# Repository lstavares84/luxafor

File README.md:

# SIGNA

Luz de presença USB-C para a sala — e, se você quiser, para acompanhar suas IAs.

O **modo sala** lê o Google Agenda e o Outlook e mostra se você está livre, prestes a entrar em uma reunião ou ocupado. O aviso de “prestes a entrar” é configurável no app (padrão: 5 minutos). O **modo IA** é opt-in: monitora Claude, ChatGPT e Grok e indica ocioso, processando, precisa de atenção, erro, ou limite atingido (cota de 5 h ou semanal).

Em modo misto, os LEDs 3 e 2 (topo e meio) mostram a sala e o LED 1 (baixo) mostra a IA. **OCUPADO tem prioridade máxima** e trava os três LEDs em vermelho; no v1 o LED da IA some, e isso não é configurável.

O nome **SIGNA** é provisório, até a busca de marca no INPI.

> **Estado em 22/11/2026:** projeto de placa (rev D) verificado no KiCad 9.0.2 (ERC 0, DRC 0 erros). Montagem 3D integrada (placa + corpo + cabo) sem interferências não intencionais. Firmware compila (≈ 17,5 KB) e os testes de host passam. **Nada foi fabricado nem testado em silício.**

## Estados

Prioridade 1 é a mais alta.

| Prioridade | Modo | Estado | Cor | Comportamento |
|---|---|---|---|---|
| 1 | Sala | OCUPADO | `#FF3B2F` | contínuo 1,0; trava os 3 LEDs (`0xFF`) |
| 2 | Sala | PRESTES A ENTRAR | `#FF8A1A` | pulso lento de 3 s; padrão 5 min antes do evento |
| 3 | IA | ERRO | `#FF3FC8` | 2,5 Hz com pulso de 130 ms (abaixo do limite WCAG de 3 Hz) |
| 4 | IA | PRECISA DE ATENÇÃO | `#FFE02E` | onda quadrada 1 Hz |
| 5 | IA | PROCESSANDO | `#3D8BFF` | respiração 2,4 s |
| 6 | IA | LIMITE ATINGIDO | `#9B5CFF` | cota de 5 h: pulso duplo; cota semanal: contínuo 0,28 |
| 7 | Sala | LIVRE | `#2FD28A` | contínuo 0,28 |
| 8 | IA | IA DESOCUPADA | `#7C8EA6` | contínuo 0,08 |

A tabela completa, com curvas e alocação dos LEDs, está em [`software/data/produto.json`](software/data/produto.json) e no [caderno conceitual](docs/caderno-signa/signa-conceito.pdf).

## Mapa do repositório

| Caminho | O que é |
|---|---|
| [`hardware/revD/`](hardware/revD/) | Placa atual: KiCad 9, gerbers, BOM, renders, [`CHANGELOG.md`](hardware/revD/CHANGELOG.md) |
| [`mecanica/`](mecanica/) | Corpo plástico, berço, tampa, botão, cabo e o conjunto integrado |
| [`software/`](software/) | Firmware (STM32C071 + TinyUSB) e app de desktop (calendário, hooks, extensão) |
| [`docs/caderno-signa/`](docs/caderno-signa/) | Caderno conceitual SIGNA (14 lâminas A3) e os scripts que o geram |
| [`docs/caderno-engenharia/`](docs/caderno-engenharia/) | Caderno de engenharia SIGNA (141 lâminas A3), em [três partes](docs/caderno-engenharia/README.md), e o gerador |
| [`docs/prompts/`](docs/prompts/) | Prompts para cadernos: [conceitual](docs/prompts/prompt-caderno-conceitual.md), [conceitual genérico](docs/prompts/prompt-caderno-generico.md) e [engenharia](docs/prompts/prompt-caderno-engenharia.md) |
| [`docs/FUNCIONAMENTO.md`](docs/FUNCIONAMENTO.md) | Relatório da engenharia reversa do Luxafor Flag |
| [`PROTOCOLO.md`](PROTOCOLO.md) | Protocolo HID de 8 bytes (o SIGNA é compatível e o estende) |
| [`luxafor.py`](luxafor.py), [`tools/anim.py`](tools/anim.py) | CLI e ferramenta de medição do Flag original |
| [`.old/`](.old/) | Revisões e conceitos superados (rev A–C, caderno antigo, exploração de formas) |

## Placa rev D

11 × 44 mm (15,2 mm nas orelhas da ponta USB), FR-4 de 2 camadas e 0,8 mm. MCU STM32C071G8U6, 3× WS2816B-2020 (16 bits por canal, PWM 10 kHz), USB-C, botão S1 na borda de baixo e pontos de teste no verso.

O que entrou em relação à rev C, o delta de custo e as pendências: [`hardware/revD/CHANGELOG.md`](hardware/revD/CHANGELOG.md).

### Placa anotada

*Face de cima: LEDs WS2816B-2020, conversor de nível, MCU, LDO, USB-C e o botão S1 na borda de baixo.*

*Face de baixo: pads SWD (Tag-Connect), jumper BOOT0, pontos de teste (VBUS, dado dos LEDs, GND) e serigrafia «SIGNA rev D».*

## Montagem 3D

Conjunto integrado — PCB rev D, corpo plástico e cabo USB-C — em um único arquivo:

- [`mecanica/signa_conjunto.glb`](mecanica/signa_conjunto.glb) (~9 MB), para ver no navegador ([visualizador glTF](https://gltf-viewer.donmccurdy.com))
- [`mecanica/signa_conjunto.step`](mecanica/signa_conjunto.step) (~14 MB), para o CAD

Desenhos técnicos (A00, P01–P06), STEP/STL/3MF de cada peça e a BOM: [`mecanica/README.md`](mecanica/README.md).

<table>
  <tr>
    <td align="center" width="50%">
      <br>
      <strong>Em uso · OCUPADO</strong>
    </td>
    <td align="center" width="50%">
      <br>
      <strong>Em uso · LIVRE</strong>
    </td>
  </tr>
  <tr>
    <td align="center">
      <br>
      <strong>Isométrica</strong>
    </td>
    <td align="center">
      <br>
      <strong>Explodida</strong>
    </td>
  </tr>
  <tr>
    <td align="center">
      <br>
      <strong>Corte</strong>
    </td>
    <td align="center">
      <br>
      <strong>Encaixe USB-C</strong>
    </td>
  </tr>
</table>

## Software

Firmware e app estão em [`software/`](software/). Como compilar, gravar e configurar: [`software/docs/README.md`](software/docs/README.md). Arquitetura e protocolo: [`software/docs/arquitetura.md`](software/docs/arquitetura.md).

- **Firmware** (C, STM32C071G8U6 + TinyUSB): motor dos estados, WS2816 a 48 bits/LED, DFU na ROM, serial em flash. Compila em ≈ 17,5 KB de flash. A placa atual é a rev D (mesmos pinos de USB e LEDs da rev C; o S1 entra em PA14).
- **App** (Python 3.10+): daemon, CLI, bandeja, calendários Google e Outlook, hooks de Claude Code / Codex e extensão para ChatGPT, Claude e Grok na web.
- Compatível com o protocolo HID de 8 bytes do Luxafor Flag, com extensões (serial `0x51`/`0x52`/`0x62`, estados por LED).

Ainda não há teste em silício. O VID:PID padrão de desenvolvimento é `1209:0001` (pid.codes, só para prototipagem).

## Decisões em aberto

1. **Posição do botão.** Embaixo do pendente, é preciso segurar o tubo para apertar (a chave pede 1,6 N; o pendente pesa ~0,2 N). Alternativas: chave mais leve, ou o botão na tampa (exigiria flex ou fio).
2. **DFU pelo botão.** Só funciona se `nBOOT_SEL = 0` for gravado na produção. Isso se junta à decisão já aberta no software (`make AUTO_NBOOT_SEL=1` ou gravação dos option bytes).
3. **Cabo.** Para cotar: casca metálica do plugue exposta ≥ 5,8 mm, sobremoldagem ≤ 11,6 × 6,4 mm, capa Ø 3,5–4,0 mm. Vale pedir amostra ao fornecedor.
4. **Painel de fabricação.** A placa tem 15,2 mm de largura nas orelhas, e elas não podem quebrar na separação.
5. **Estoque do MCU.** A JLC tinha 109 unidades do STM32C071G8U6 em 22/11/2026: dá para os protótipos, fica apertado para produção. A alternativa GBU6 estava com estoque zero. Evitar as variantes com sufixo «N».
6. **VID:PID definitivo** e busca de marca **SIGNA** no INPI.
7. Ainda falta validar como os limites da web (5 h e semanal) das IAs são detectados.

## Engenharia reversa do Luxafor Flag

Este repositório começou como a engenharia reversa do [Luxafor Flag](https://luxafor.com/product/flag2/) (USB `04d8:f372`, firmware `0x3c`). Essa parte permanece e o SIGNA é compatível com o mesmo protocolo HID.

```bash
./luxafor.py version                 # firmware 0x3c
./luxafor.py color top blue          # LEDs: all | bottom | middle | top
./luxafor.py fade all green 20 --wait
./luxafor.py strobe all red 10 3
./luxafor.py wave 1 cyan 5 60
./luxafor.py pattern rainbow --wait
./luxafor.py off
```

Permissão: o usuário precisa de leitura e escrita em `/dev/hidrawN`.

**Cuidados com o Flag original:** `01 13 …` (endereço `0x13`) trava o firmware — reconecte o aparelho fisicamente; **não** use reset USB por software (`USBDEVFS_RESET`), que já travou o barramento do host. `0x51` e `0x52` **gravam o serial na NVM** (6 bytes e os 4 primeiros, respectivamente); `0x62` só lê. Não envie `0x51`/`0x52` em um aparelho cujo serial você queira preservar. Os opcodes `0x05` e `0x07`–`0x0F` não existem (não há resposta).

## Material antigo

Revisões de placa A–C, o caderno conceitual anterior e a exploração das quatro formas de produto estão em [`.old/`](.old/). Veja [`.old/README.md`](.old/README.md) para o que tem lá e por quê.

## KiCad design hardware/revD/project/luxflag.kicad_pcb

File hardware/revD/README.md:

# SIGNA, placa rev D (KiCad 9.0.2)

Evolução da rev C ([`.old/hardware/revC/`](../../.old/hardware/revC/)). **O que mudou e por quê: ver [`CHANGELOG.md`](CHANGELOG.md).** Tudo é gerado por script a partir de `tools/netlist.py`.
Apresentação completa, galeria e tabela de estados: ver o [README do repositório](../../README.md).

| Item | Valor |
|---|---|
| Placa | 11 × 44 mm (15,2 mm nas orelhas da ponta USB), FR-4, 2 camadas, 0,8 mm, 1 oz; USB-C sobressai 0,65 mm |
| Botão | S1 ALPS SKRTLAE010 lateral (C110293) na borda de baixo + R5 1 kΩ para PA14: OCUPADO/LIVRE manual e DFU ao ligar |
| Teste | TP1 VBUS, TP2 dado LEDs 5 V, TP3 GND (face de baixo) |
| LEDs | 3× **WS2816B-2020** (Worldsemi, LCSC C4154877): 16 bit/canal + gamma 4 bit, PWM 10 kHz, 20 mA (R+G+B), 6 pinos com dado duplo BI/BO |
| MCU | STM32C071G8U6 (UFQFPN-28 4×4, C44521811), USB FS sem cristal, DFU na ROM |
| Nível | SN74AHCT1G125DBVR (TI, SOT-23-5, C7484): VIH 2 V com VCC 5 V; WS2816 exige VIH ≥ 0,7×VDD = 3,5 V |
| Energia | VBUS 5 V nos LEDs e no buffer; AP2112K-3.3 (C51118) no MCU. Consumo estimado ≤ ~70 mA (3 × 20 mA + MCU) |
| USB | HRO TYPE-C-31-M-12 (C165948), CC1/CC2 5,1 kΩ, USBLC6-2SC6 (C7519) |
| SWD / BOOT0 | Tag-Connect TC2030-IDC-NL na face de baixo; JP1 (jumper de solda NA) + R4 1 kΩ puxam PA14/BOOT0 a 3V3 |
| Verificação | ERC 0. DRC 0 erros, 0 pendências, paridade OK; 1 aviso (silk do USB-C editado de propósito) |
| Roteamento | Freerouting 2.1.0 (DSN/SES, `-mt 1`, MP=80), 342 trilhas, 24 vias, + [`fix_vias.py`](tools/fix_vias.py) + remoção de trechos duplicados e pontas soltas |

## Ligação dos LEDs (datasheet WS2816B-2020, "Typical Application Circuit")
`U3.Y → R3 33 Ω → D1.DI`; `D1.BI = GND`; `Dn.DO → Dn+1.DI`; `Dn.BO → Dn+1.BI`; `D3.DO` e `D3.BO` livres.
Firmware: 48 bits por LED (G16 R16 B16, MSB primeiro), T0H 200–320 ns, T1H 520–800 ns, reset > 280 µs.

## Regenerar
```
cd tools
python3 gen_sch.py
python3 models3d.py             # modelos 3D próprios em ../lib/3d
MP=80 ./route.sh -mt 1         # placa (com orelhas) + DSN + Freerouting + SES + fix_vias + limpeza + GND + DRC
# (retrofit_outline.py só troca o Edge.Cuts de uma placa já roteada, sem rerotear)
python3 export_jlc.py          # fab/gerber.zip, bom.csv, cpl.csv
kicad-cli sch export pdf -o ../luxflag-schematic.pdf ../project/luxflag.kicad_sch
bash render_views.sh && python3 finish_views.py   # vistas 3D + close-ups
bash copper_views.sh                              # camadas de cobre (SVG -> PNG via Chrome)
python3 annotate.py                               # renders anotados
python3 parts_check.py                            # estoque LCSC/JLC -> docs/parts-check.json
```
O Freerouting 2.1.0 (jar) não vai no pacote: baixe de github.com/freerouting/freerouting/releases.

## Pendências
1. Rotação do CPL na prévia da JLC (U1–U4, J1, D1–D3).
2. Footprint do WS2816B-2020 feito pelo datasheet; conferir na prévia.
3. BOOT0 (JP1 ou botão S1 ao ligar) só vale com `nBOOT_SEL = 0`; com flash vazia entra em DFU sozinho.
5. Painel: considerar as orelhas (15,2 mm) no trilho/V-cut.
6. Firmware: botão lido pelo IDR de PA14 em modo SWCLK (ver CHANGELOG).
4. Pinos 18/19 = PA11[PA9]/PA12[PA10]: confirmar remapeamento no firmware.
5. Modelos 3D de U1, J1 e LEDs nos renders são substitutos visuais.
6. Par USB sem impedância controlada (FS, < 15 mm).

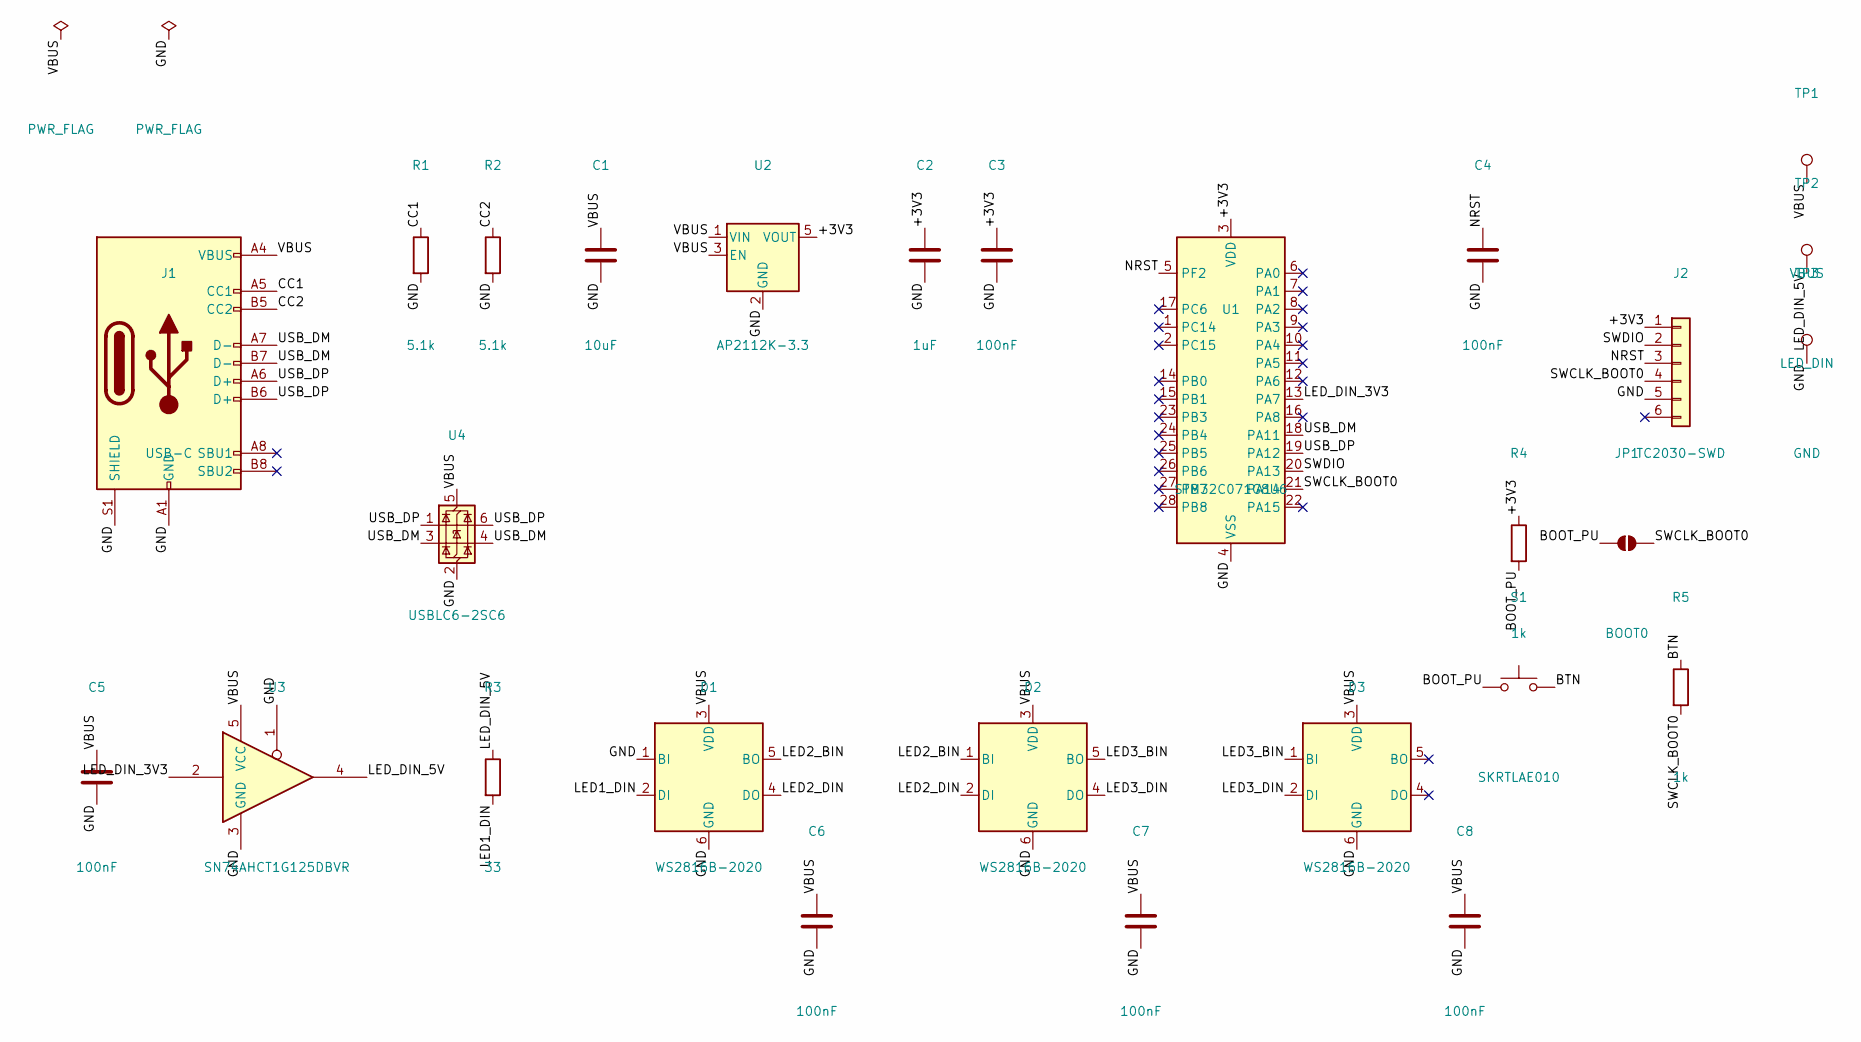
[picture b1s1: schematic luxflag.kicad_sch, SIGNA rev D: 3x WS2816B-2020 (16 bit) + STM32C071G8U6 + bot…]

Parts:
C1: 10uF; C_0603_1608Metric; LCSC C19702
C2: 1uF; C_0402_1005Metric; LCSC C52923
C3, C4, C5, C6, C7, C8: 100nF; C_0402_1005Metric; LCSC C1525
D1, D2, D3: WS2816B-2020; LED_WS2816B-2020_2.2x2.0mm; LCSC C4154877
J1: USB-C; USB_C_Receptacle_HRO_TYPE-C-31-M-12; LCSC C165948
J2: TC2030-SWD; Tag-Connect_TC2030-IDC-NL_2x03_P1.27mm_Vertical
JP1: BOOT0; SolderJumper-2_P1.3mm_Open_RoundedPad1.0x1.5mm
R1, R2: 5.1k; R_0402_1005Metric; LCSC C25905
R3: 33; R_0402_1005Metric; LCSC C25105
R4, R5: 1k; R_0402_1005Metric; LCSC C11702
S1: SKRTLAE010; SW_SKRTLAE010_JLC; LCSC C110293
TP1: VBUS; TestPoint_Pad_D1.0mm
TP2: LED_DIN; TestPoint_Pad_D1.0mm
TP3: GND; TestPoint_Pad_D1.0mm
U1: STM32C071G8U6; QFN-28_4x4mm_P0.5mm; LCSC C44521811
U2: AP2112K-3.3; SOT-23-5; LCSC C51118
U3: SN74AHCT1G125DBVR; SOT-23-5; LCSC C7484
U4: USBLC6-2SC6; SOT-23-6; LCSC C7519

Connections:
/+3V3: C2.1, C3.1, J2.1, R4.1, U1.3 (VDD), U2.5 (VOUT)
/BOOT_PU: JP1.1 (A), R4.2, S1.1
/BTN: R5.1, S1.2
/CC1: J1.A5 (CC1), R1.1
/CC2: J1.B5 (CC2), R2.1
/GND: C1.2, C2.2, C3.2, C4.2, C5.2, C6.2, C7.2, C8.2, D1.1 (BI), D1.6 (GND), D2.6 (GND), D3.6 (GND), J1.A1 (GND), J1.A12 (GND), J1.B1 (GND), J1.B12 (GND), J1.S1 (SHIELD), J2.5, R1.2, R2.2, TP3.1, U1.4 (VSS), U2.2 (GND), U3.1, U3.3 (GND), U4.2 (GND)
/LED1_DIN: D1.2 (DI), R3.2
/LED2_BIN: D1.5 (BO), D2.1 (BI)
/LED2_DIN: D1.4 (DO), D2.2 (DI)
/LED3_BIN: D2.5 (BO), D3.1 (BI)
/LED3_DIN: D2.4 (DO), D3.2 (DI)
/LED_DIN_3V3: U1.13 (PA7), U3.2
/LED_DIN_5V: R3.1, TP2.1, U3.4
/NRST: C4.1, J2.3, U1.5 (PF2)
/SWCLK_BOOT0: J2.4, JP1.2 (B), R5.2, U1.21 (PA14)
/SWDIO: J2.2, U1.20 (PA13)
/USB_DM: J1.A7 (D-), J1.B7 (D-), U1.18 (PA11), U4.3 (I/O2), U4.4 (I/O2)
/USB_DP: J1.A6 (D+), J1.B6 (D+), U1.19 (PA12), U4.1 (I/O1), U4.6 (I/O1)
/VBUS: C1.1, C5.1, C6.1, C7.1, C8.1, D1.3 (VDD), D2.3 (VDD), D3.3 (VDD), J1.A4 (VBUS), J1.A9 (VBUS), J1.B4 (VBUS), J1.B9 (VBUS), TP1.1, U2.1 (VIN), U2.3 (EN), U3.5 (VCC), U4.5 (VBUS)

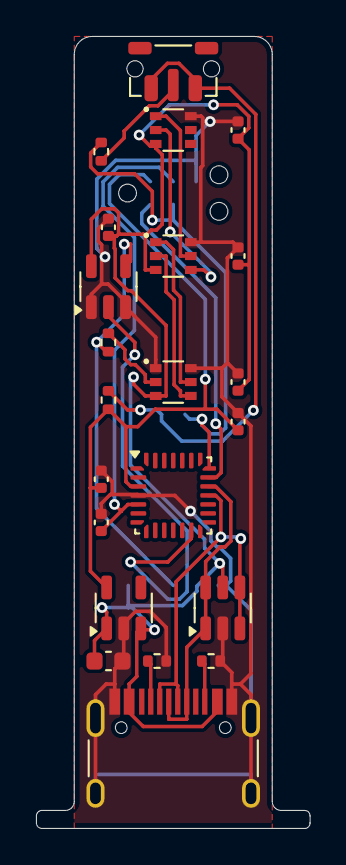
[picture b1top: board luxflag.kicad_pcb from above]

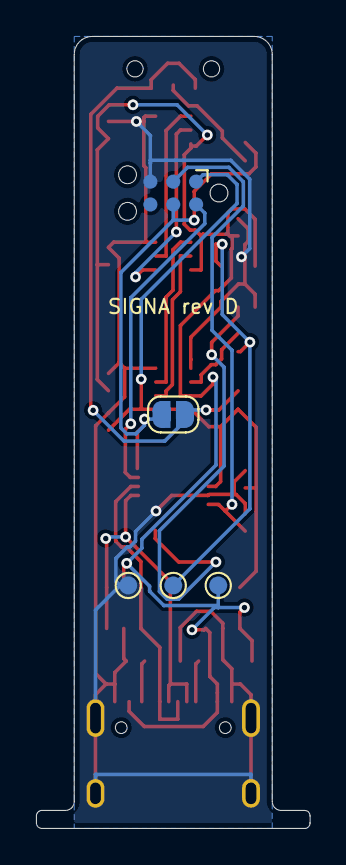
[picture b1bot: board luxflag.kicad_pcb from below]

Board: 2 copper layers, 15.2 x 44.0 mm, 27 parts (5 on the bottom side), 19 nets.

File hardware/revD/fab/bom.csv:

Comment,Designator,Footprint,LCSC
10uF,C1,C_0603_1608Metric,C19702
1uF,C2,C_0402_1005Metric,C52923
100nF,"C3,C4,C5,C6,C7,C8",C_0402_1005Metric,C1525
WS2816B-2020,"D1,D2,D3",LED_WS2816B-2020_2.2x2.0mm,C4154877
USB-C,J1,USB_C_Receptacle_HRO_TYPE-C-31-M-12,C165948
5.1k,"R1,R2",R_0402_1005Metric,C25905
33,R3,R_0402_1005Metric,C25105
1k,"R4,R5",R_0402_1005Metric,C11702
SKRTLAE010,S1,SW_SKRTLAE010_JLC,C110293
STM32C071G8U6,U1,QFN-28_4x4mm_P0.5mm,C44521811
AP2112K-3.3,U2,SOT-23-5,C51118
SN74AHCT1G125DBVR,U3,SOT-23-5,C7484
USBLC6-2SC6,U4,SOT-23-6,C7519

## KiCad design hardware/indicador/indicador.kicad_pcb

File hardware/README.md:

# Hardware SIGNA

A placa atual é a **[rev D](revD/)**: STM32C071G8U6, 3× WS2816B-2020 (16 bits por canal), botão S1 na borda de baixo, pontos de teste no verso e orelhas na ponta do USB para travar a placa no berço.

| Item | Valor |
|---|---|
| Placa | 11 × 44 mm (15,2 mm nas orelhas), FR-4, 2 camadas, 0,8 mm |
| MCU | STM32C071G8U6 (UFQFPN-28), USB FS sem cristal, DFU na ROM |
| LEDs | 3× WS2816B-2020, dado em PA7 via SN74AHCT1G125 |
| Botão | S1 ALPS SKRTLAE010 em PA14: alterna OCUPADO/LIVRE; segurado ao ligar, entra em DFU (`nBOOT_SEL = 0`) |
| Estado | KiCad 9.0.2, ERC 0, DRC 0 erros — **ainda não fabricada nem testada em silício** |

Arquivos de fabricação, esquemático, BOM, gerbers, renders e o que mudou em relação à rev C: [`revD/README.md`](revD/README.md) e [`revD/CHANGELOG.md`](revD/CHANGELOG.md).

A montagem 3D integrada (placa + corpo + cabo) está em [`mecanica/`](../mecanica/).

Revisões anteriores (rev A / indicador, rev B e rev C) e as ferramentas da rev A foram para [`.old/hardware/`](../.old/hardware/).

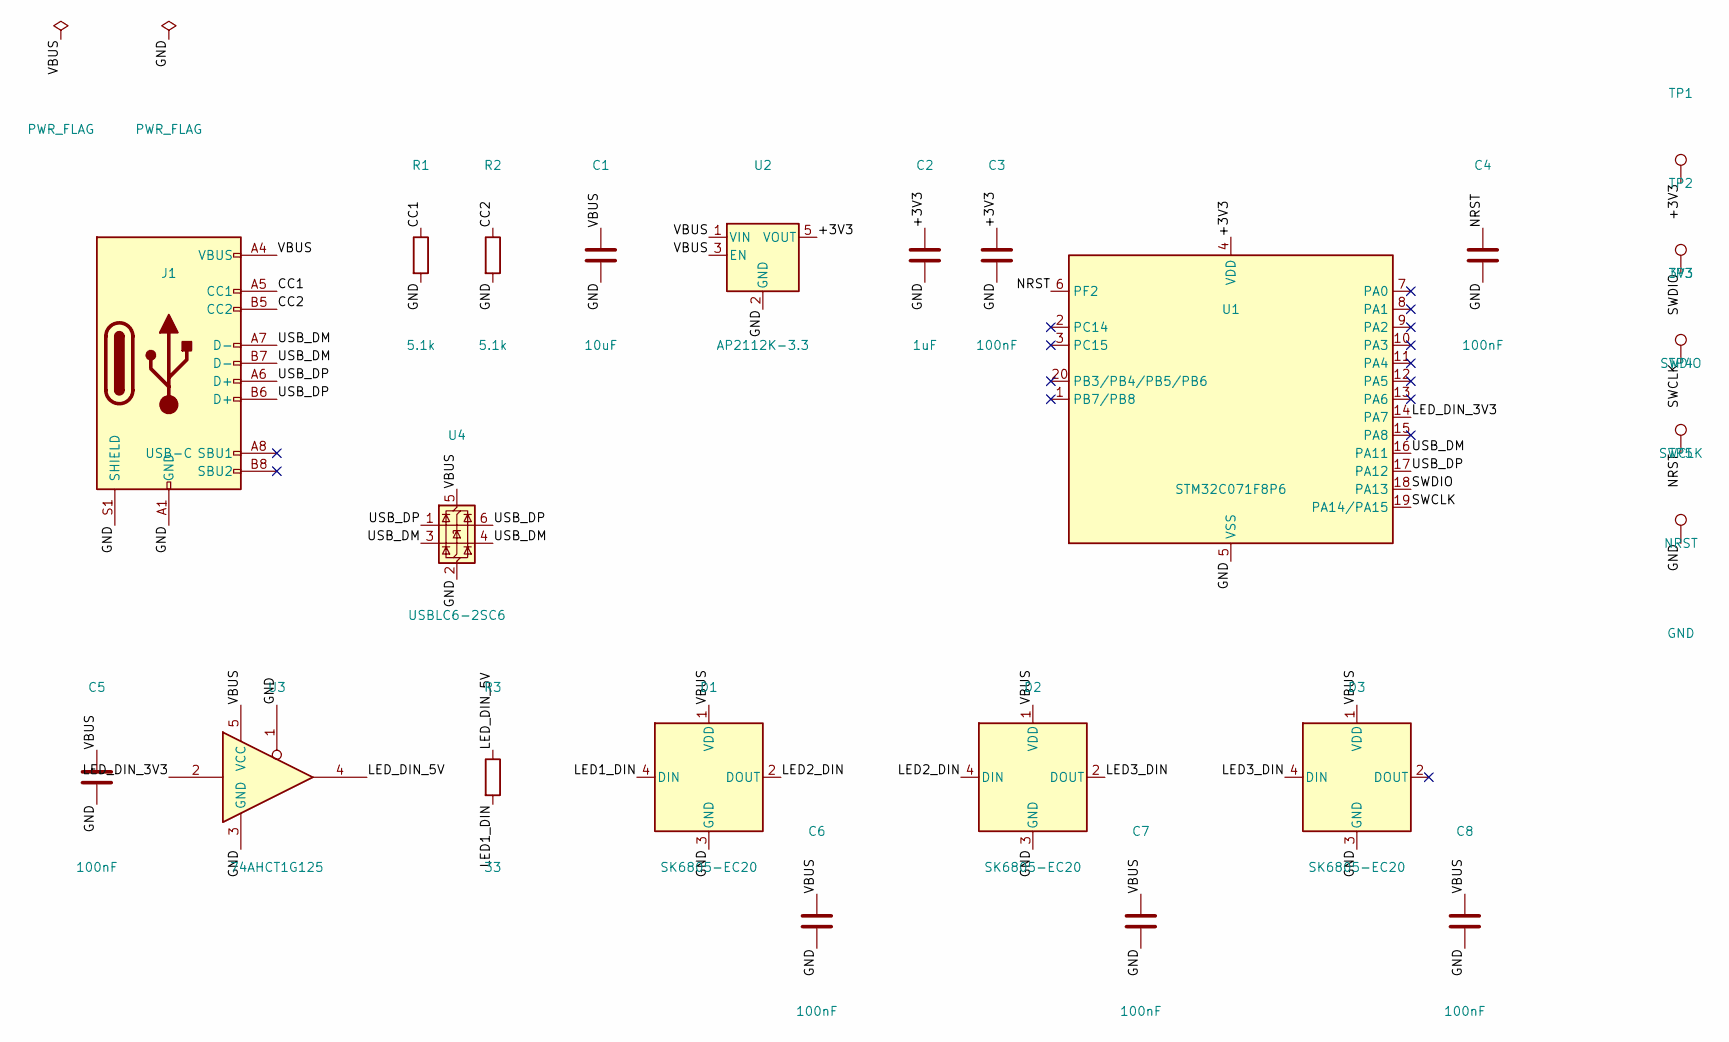
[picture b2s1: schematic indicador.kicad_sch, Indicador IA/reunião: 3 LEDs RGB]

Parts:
C1: 10uF; C_0603_1608Metric; LCSC C19702
C2: 1uF; C_0402_1005Metric; LCSC C52923
C3, C4, C5, C6, C7, C8: 100nF; C_0402_1005Metric; LCSC C1525
D1, D2, D3: SK6805-EC20; LED_SK6805-EC20_2.0x2.0mm; LCSC C2890036
J1: USB-C; USB_C_Receptacle_HRO_TYPE-C-31-M-12; LCSC C165948
R1, R2: 5.1k; R_0402_1005Metric; LCSC C25905
R3: 33; R_0402_1005Metric; LCSC C25105
TP1: 3V3; TestPoint_Pad_D1.0mm
TP2: SWDIO; TestPoint_Pad_D1.0mm
TP3: SWCLK; TestPoint_Pad_D1.0mm
TP4: NRST; TestPoint_Pad_D1.0mm
TP5: GND; TestPoint_Pad_D1.0mm
U1: STM32C071F8P6; TSSOP-20_4.4x6.5mm_P0.65mm; LCSC C43650205
U2: AP2112K-3.3; SOT-23-5; LCSC C51118
U3: 74AHCT1G125; SOT-353_SC-70-5; LCSC C53114384
U4: USBLC6-2SC6; SOT-23-6; LCSC C7519

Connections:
/+3V3: C2.1, C3.1, TP1.1, U1.4 (VDD), U2.5 (VOUT)
/CC1: J1.A5 (CC1), R1.1
/CC2: J1.B5 (CC2), R2.1
/GND: C1.2, C2.2, C3.2, C4.2, C5.2, C6.2, C7.2, C8.2, D1.3 (GND), D2.3 (GND), D3.3 (GND), J1.A1 (GND), J1.A12 (GND), J1.B1 (GND), J1.B12 (GND), J1.S1 (SHIELD), R1.2, R2.2, TP5.1, U1.5 (VSS), U2.2 (GND), U3.1, U3.3 (GND), U4.2 (GND)
/LED1_DIN: D1.4 (DIN), R3.2
/LED2_DIN: D1.2 (DOUT), D2.4 (DIN)
/LED3_DIN: D2.2 (DOUT), D3.4 (DIN)
/LED_DIN_3V3: U1.14 (PA7), U3.2
/LED_DIN_5V: R3.1, U3.4
/NRST: C4.1, TP4.1, U1.6 (PF2)
/SWCLK: TP3.1, U1.19 (PA14/PA15)
/SWDIO: TP2.1, U1.18 (PA13)
/USB_DM: J1.A7 (D-), J1.B7 (D-), U1.16 (PA11), U4.3 (I/O2), U4.4 (I/O2)
/USB_DP: J1.A6 (D+), J1.B6 (D+), U1.17 (PA12), U4.1 (I/O1), U4.6 (I/O1)
/VBUS: C1.1, C5.1, C6.1, C7.1, C8.1, D1.1 (VDD), D2.1 (VDD), D3.1 (VDD), J1.A4 (VBUS), J1.A9 (VBUS), J1.B4 (VBUS), J1.B9 (VBUS), U2.1 (VIN), U2.3 (EN), U3.5 (VCC), U4.5 (VBUS)

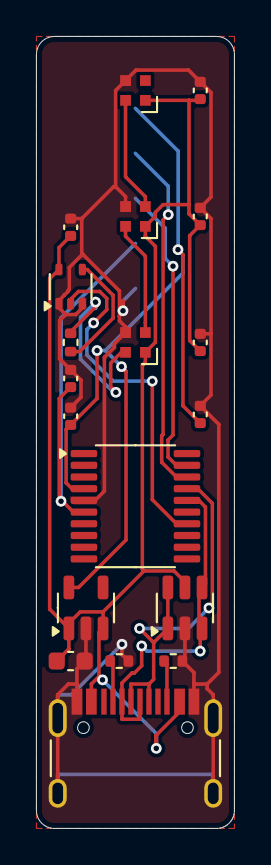
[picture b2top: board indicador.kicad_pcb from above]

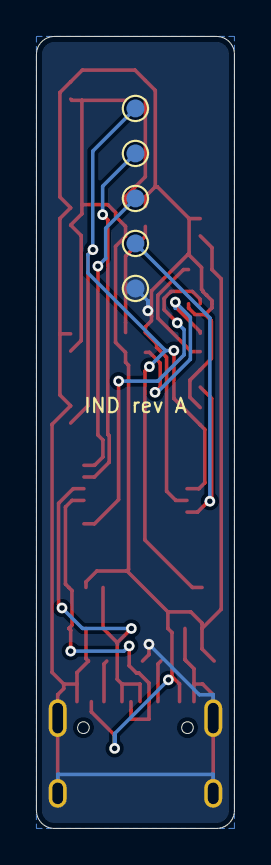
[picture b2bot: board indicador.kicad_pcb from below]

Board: 2 copper layers, 11.0 x 44.0 mm, 24 parts (5 on the bottom side), 15 nets.

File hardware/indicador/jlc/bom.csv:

Comment,Designator,Footprint,LCSC
10uF,C1,C_0603_1608Metric,C19702
1uF,C2,C_0402_1005Metric,C52923
100nF,"C3,C4,C5,C6,C7,C8",C_0402_1005Metric,C1525
SK6805-EC20,"D1,D2,D3",LED_SK6805-EC20_2.0x2.0mm,C2890036
USB-C,J1,USB_C_Receptacle_HRO_TYPE-C-31-M-12,C165948
5.1k,"R1,R2",R_0402_1005Metric,C25905
33,R3,R_0402_1005Metric,C25105
STM32C071F8P6,U1,TSSOP-20_4.4x6.5mm_P0.65mm,C43650205
AP2112K-3.3,U2,SOT-23-5,C51118
74AHCT1G125,U3,SOT-353_SC-70-5,C53114384
USBLC6-2SC6,U4,SOT-23-6,C7519

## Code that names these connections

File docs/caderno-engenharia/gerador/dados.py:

"""Leitura das fontes de engenharia. Nada inventado: se faltar, o chamador marca 'a definir'."""
import csv, json, os, sys

ROOT = os.path.dirname(os.path.abspath(__file__))


def _pasta(env, relativos, reserva):
    """Caminho da fonte: SIGNA_* se definida; senão a pasta deste repositório; senão /workspace."""
    v = os.environ.get(env, '').strip()
    if v:
        return v
    raiz = os.path.abspath(os.path.join(ROOT, '..', '..', '..'))
    for rel in relativos:
        p = os.path.join(raiz, rel)
        if os.path.isdir(p):
            return p
    return reserva


REV_D = _pasta('SIGNA_REVD', ('hardware/revD',), '/workspace/luxpcb-revD')
SW = _pasta('SIGNA_SW', ('software',), '/workspace/signa-sw')
MECH = _pasta('SIGNA_MECH', ('mecanica',), '/workspace/signa-3d')
CONC = _pasta('SIGNA_CONC', ('docs/caderno-signa', '.old/docs/conceito'), '/workspace/caderno-revC')

produto = json.load(open(os.path.join(CONC, 'dados/produto.json')))
jlc_revd = json.load(open(os.path.join(REV_D, 'docs/jlc_revD_2026-11-22.json')))
estoque = json.load(open(os.path.join(REV_D, 'docs/estoque_stm32c071.json')))
parts = json.load(open(os.path.join(REV_D, 'docs/parts-check.json')))
folgas_doc = json.load(open(os.path.join(MECH, 'docs/verificacao_montagem.json')))

# BOM eletrônica (fab)
bom_elec = list(csv.DictReader(open(os.path.join(REV_D, 'fab/bom.csv'))))
cpl = list(csv.DictReader(open(os.path.join(REV_D, 'fab/cpl.csv'))))

# BOM completa do produto
bom_prod = list(csv.DictReader(open(os.path.join(MECH, 'bom/bom_completa.csv'))))

modos = {m['id']: m for m in produto['modos']}
MODOS_PRIO = [modos[i] for i in produto['prioridade_ordem']]

# Pinagem UFQFPN-28 GP (DS14693, figura do encapsulamento _GxU, não N)
MCU_PINS = [
    (1, 'PC14-OSCX_IN', 'NC', 'não conectar'),
    (2, 'PC15-OSCX_OUT', 'NC', 'não conectar'),
    (3, 'VDD/VDDA', '+3V3', 'alimentação do MCU (U2)'),
    (4, 'VSS/VSSA', 'GND', 'terra'),
    (5, 'PF2-NRST', 'NRST', 'reset; C4 100 nF a GND; J2 pino 3'),
    (6, 'PA0', 'NC', 'não conectar'),
    (7, 'PA1', 'NC', 'não conectar'),
    (8, 'PA2', 'NC', 'não conectar'),
    (9, 'PA3', 'NC', 'não conectar'),
    (10, 'PA4', 'NC', 'não conectar'),
    (11, 'PA5', 'NC', 'não conectar'),
    (12, 'PA6', 'NC', 'não conectar'),
    (13, 'PA7', 'LED_DIN_3V3', 'SPI1_MOSI (AF0) → U3.A; dado dos LEDs'),
    (14, 'PB0', 'NC', 'não conectar'),
    (15, 'PB1', 'NC', 'não conectar'),
    (16, 'PA8', 'NC', 'não conectar'),
    (17, 'PC6', 'NC', 'no GP é PC6; na versão N este pino é VDDIO2 — não trocar'),
    (18, 'PA11 [PA9]', 'USB_DM', 'USB FS D− (padrão no UFQFPN-28; não remapear)'),
    (19, 'PA12 [PA10]', 'USB_DP', 'USB FS D+ (padrão; não remapear)'),
    (20, 'PA13', 'SWDIO', 'J2 pino 2'),
    (21, 'PA14-BOOT0', 'SWCLK_BOOT0', 'SWCLK + BOOT0; S1/R5 e JP1; J2 pino 4'),
    (22, 'PA15', 'NC', 'não conectar'),
    (23, 'PB3', 'NC', 'não conectar'),
    (24, 'PB4', 'NC', 'não conectar'),
    (25, 'PB5', 'NC', 'não conectar'),
    (26, 'PB6', 'NC', 'não conectar'),
    (27, 'PB7', 'NC', 'não conectar'),
    (28, 'PB8', 'NC', 'não conectar'),
]

# Preços JLC da BOM completa (já por produto)
def money(v):
    try:
        return float(v)
    except Exception:
        return None

# estados nativos firmware
ESTADOS_FW = [
    (0, 'apagado', '—', '—', 'LEDs apagados'),
    (1, 'LIVRE', '#2FD28A', 'fixo 0,28', 'SALA'),
    (2, 'PRESTES A ENTRAR', '#FF8A1A', 'respiração 3,0 s, piso 0,20, expoente 1,4', 'SALA'),
    (3, 'OCUPADO', '#FF3B2F', 'fixo 1,0', 'SALA'),
    (4, 'IA DESOCUPADA', '#7C8EA6', 'fixo 0,08', 'IA'),
    (5, 'PROCESSANDO', '#3D8BFF', 'respiração 2,4 s, piso 0,15, expoente 1,6', 'IA'),
    (6, 'PRECISA DE ATENÇÃO', '#FFE02E', 'quadrada 1 Hz, 50 %, piso 0,06', 'IA'),
    (7, 'ERRO', '#FF3FC8', 'estrobo 2,5 Hz, pulso 130 ms, piso 0,04', 'IA'),
    (8, 'LIMITE 5 h', '#9B5CFF', 'pulso duplo a cada 3 s (250/250/250 ms) a 0,55, piso 0,06', 'IA'),
    (9, 'LIMITE semanal', '#9B5CFF', 'fixo 0,28', 'IA'),
]

# Itens em aberto / a definir (só o que as fontes não fecham)
A_DEFINIR = [
    ('Nome comercial', 'SIGNA é provisório até verificação no INPI.'),
    ('VID:PID USB', 'Padrão de desenvolvimento 1209:0001 (Test PID do pid.codes). Par definitivo a decidir (pid.codes próprio, VID USB-IF ou sublicença). Nunca usar 04d8:f372 em unidade vendida.'),
    ('String USB do produto', 'O firmware ainda identifica o produto como "SIGNA rev C" (usb_ids.h).'),
    ('Byte de versão 0x80', 'Manter 0x3C (compatível com software antigo) ou usar um valor próprio. A versão real do SIGNA sai no 0x1F (hoje 0.1).'),
    ('nBOOT_SEL na produção', 'Precisa ser gravado como 0 para o DFU pelo botão/JP1 funcionar depois da 1.ª gravação. Processo de fábrica a definir (CubeProgrammer ou make AUTO_NBOOT_SEL=1).'),
    ('Posição do botão', 'S1 + P06 ficam embaixo do pendente. A chave pede 1,6 N e o produto pesa cerca de 0,2 N: é preciso segurar o tubo para apertar. Alternativas (chave mais leve ou botão na tampa, que exigiria flex ou fio) estão em aberto.'),
    ('Gesto longo do botão', 'O CHANGELOG da rev D sugere debounce de 30 ms e pressão longa de 2 s, e deixa o gesto longo em aberto. A leitura de PA14 ainda é pendência do firmware (nada testado em silício).'),
    ('Ordem GRB na placa', 'O driver envia G16 R16 B16 conforme o datasheet. Validar no primeiro silício: 01 FF FF 00 00 tem de acender vermelho.'),
    ('SPI/DMA contínuo', 'Validar com analisador ou osciloscópio no R3 que não há intervalo entre palavras (bit 0 ≈ 250 ns alto, bit 1 ≈ 667 ns).'),
    ('Acabamento e máscara da PCB', 'O README da rev D especifica ENIG; o arquivo gerber job está com Finish: "None". Cor da máscara (verde ou preta) não foi decidida.'),
    ('Painelização', 'A placa tem 15,2 mm de largura nas orelhas. O trilho/V-cut precisa preservar as orelhas.'),
    ('Prévia JLC', 'Conferir rotação do CPL (U1–U4, J1, D1–D3) e o footprint do WS2816B-2020 feito pelo datasheet.'),
    ('Estoque do MCU', 'STM32C071G8U6: 109 un. na JLC e 36 na LCSC em 22/11/2026. Alternativa GBU6 (128 KB, mesma pinagem GP): estoque 0 na JLC. Não usar sufixo N (pino 17 = VDDIO2).'),
    ('Amostra do cabo C01', 'Exigir amostra: casca exposta ≥ 5,8 mm, sobremolde ≤ 11,6 × 6,4 mm, sobremolde+alívio ≤ 24,5 mm, alívio ≤ Ø6,4 nos últimos 4,5 mm, capa Ø3,5 a 4,0 mm.'),
    ('Part numbers mecânicos', 'P01–P06 e C01 sem part number de fornecedor. Graus exatos de PC opalino, PC branco refletivo e TPE 60A: a verificar (materiais.md).'),
    ('Adaptador USB-A (C02)', 'Entra no custo total (US$ 0,45 @100 / 0,25 @1000). Decisão de incluir ou não está com o Lucas.'),
    ('Gravação a laser L02', 'Opcional; não entra no critério de aceite mínimo.'),
    ('Limites de IA na web (5 h / semanal)', 'Detecção por texto da página ou da mensagem de erro: heurística frágil, a validar. A extensão MV3 é experimental.'),
    ('Microfone e câmera', 'Não implementado. Fonte de "em reunião" a definir por sistema operacional.'),
    ('Ambiente e ensaios', 'Temperatura de operação e armazenamento, umidade, grau IP, altura de queda e vida do botão: não especificados nas fontes.'),
    ('Fotometria', 'Fluxo, luminância e uniformidade dos estados não foram medidos (só critério qualitativo: sem pontos quentes a 0,5 m).'),
    ('Corrente de produção', 'Orçamento 10–15 mA apagado e 70–80 mA no branco 100 % é estimativa de datasheet. Confirmar no primeiro lote e fixar o limite (reprovação > 100 mA).'),
    ('Impedância do par USB', 'Não há controle de impedância (Full Speed, trecho < 15 mm). Aceito no projeto; não é certificação.'),
    ('Certificações', 'USB-IF, CE, FCC, ANATEL, IEC 62471 e RoHS formal: não foram feitas. O caderno traz só considerações.'),
    ('Pressão de montagem do P06', 'O press-fit do tampão é 20–40 N (pacote do Pendente). A força de inserção do pino P06 no rebaixo não está quantificada além do curso e da força da chave (1,6 N).'),
]
